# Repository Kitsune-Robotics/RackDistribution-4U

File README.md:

# RackDistribution-4U

This repo contains all the firmware and hardware for the RackDistribution-4U.
If you're looking for the latest docs/builds, see our [Releases Page](https://github.com/Kitsune-Robotics/RackDistribution-4U/releases).

# Getting Started

First, clone this repo (and optionally checkout a branch)

```shell
git clone https://github.com/Kitsune-Robotics/RackDistribution-4U.git --recursive
cd RackDistribution-4U
```

# Init Submodules

Some libraries and resources are included as submodules, run the following
command to initialize them before opening the main sch

(If you get a missing library error, make sure to do this)

```shell
git submodule update --init --recursive
```

## Project Layout

If you want to use this project template for yourself, you can find it [here!](https://github.com/Kitsune-Robotics/Project-Template)

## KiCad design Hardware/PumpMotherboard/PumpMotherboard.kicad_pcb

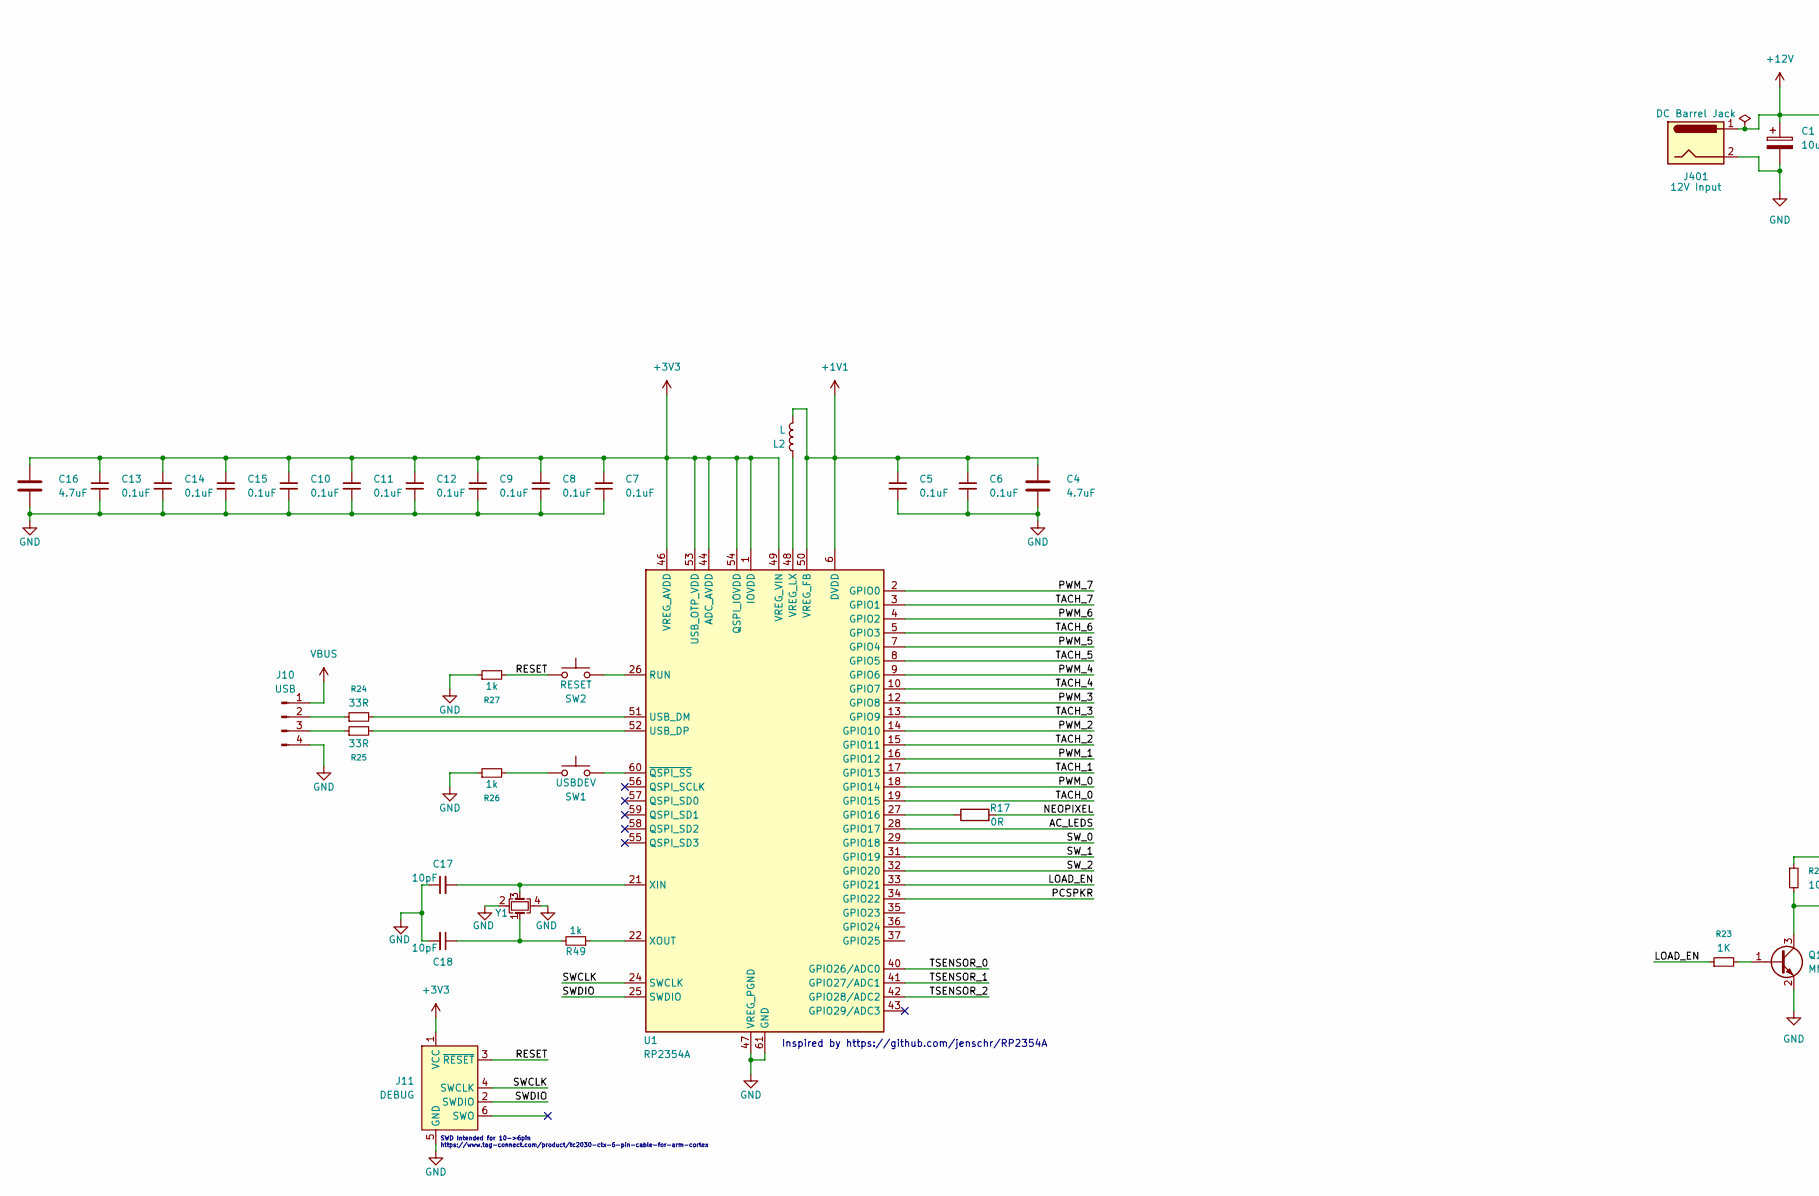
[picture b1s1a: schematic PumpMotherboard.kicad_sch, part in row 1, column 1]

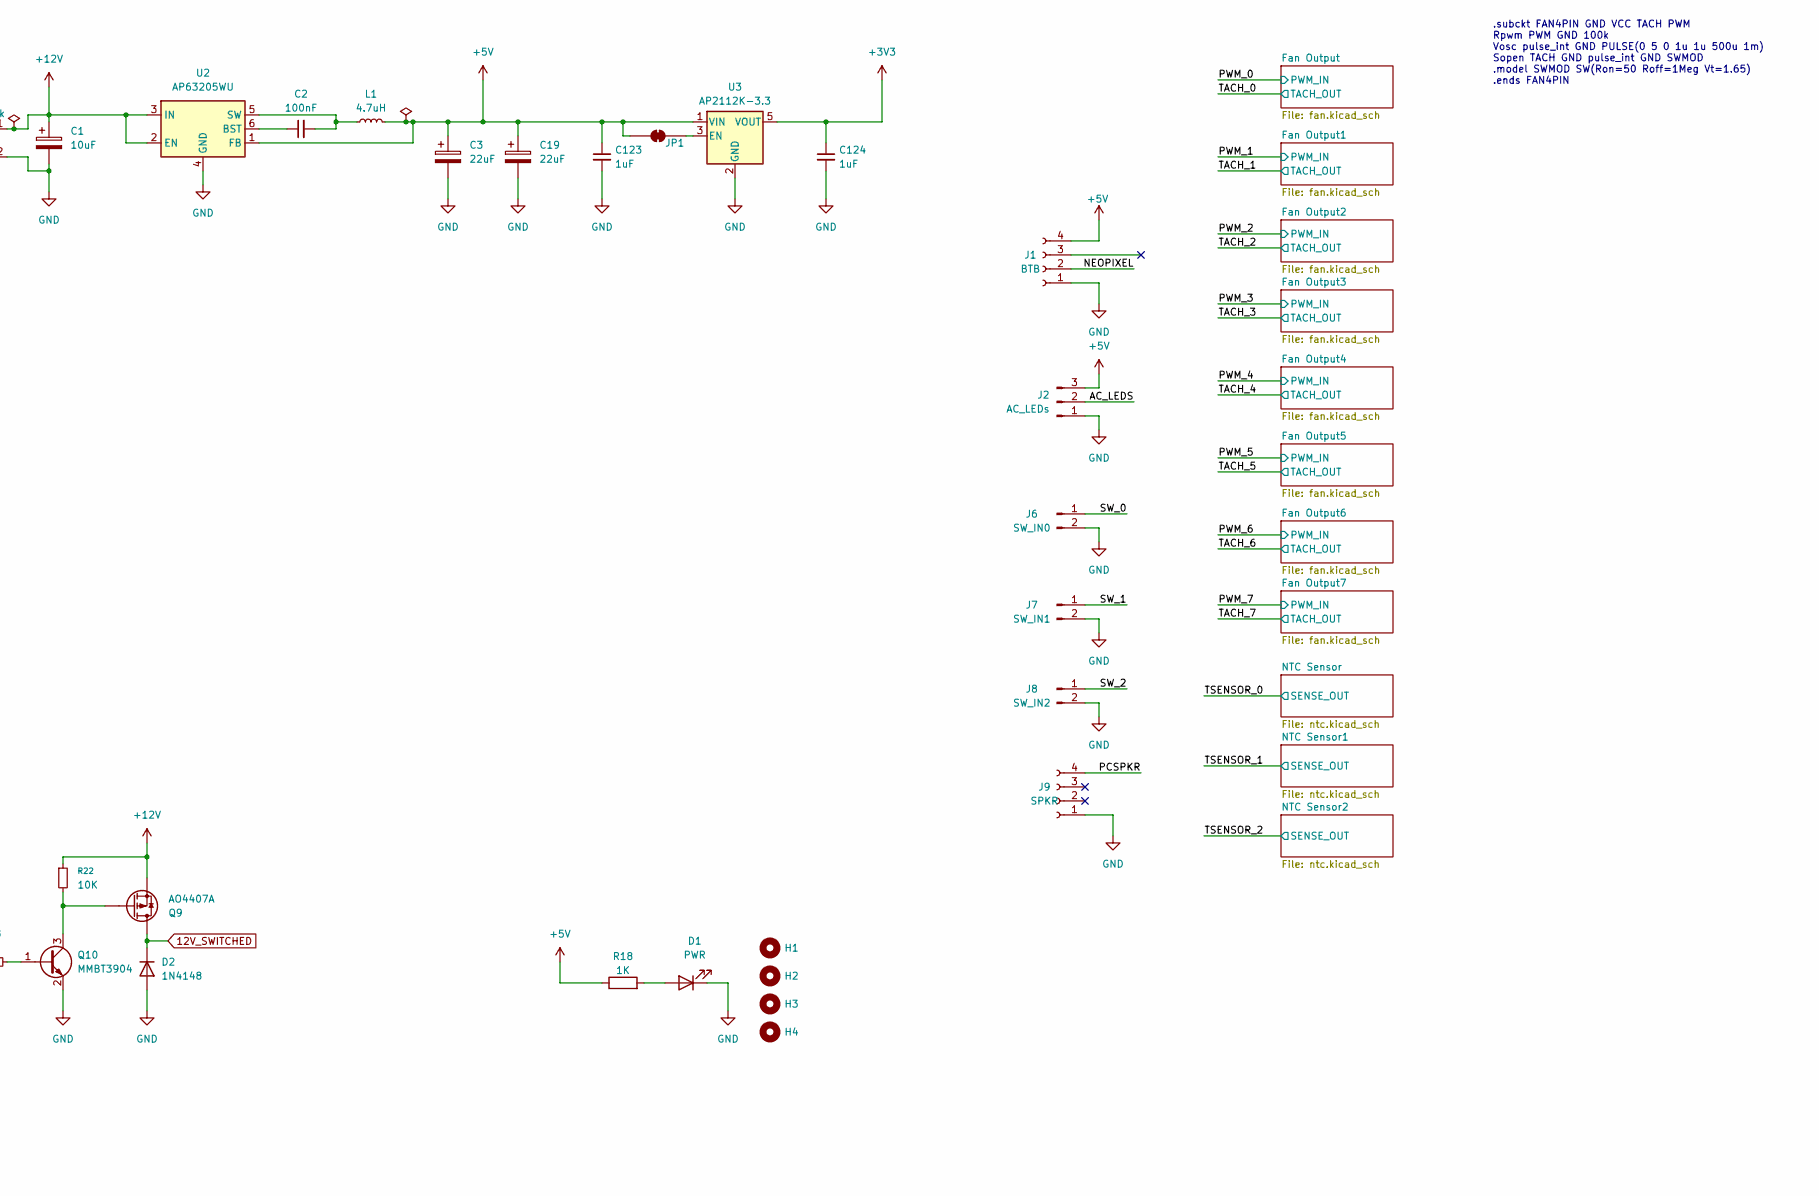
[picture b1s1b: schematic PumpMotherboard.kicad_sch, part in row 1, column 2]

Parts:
C1: 10uF; CP_Elec_4x3
C2: 100nF; C_0805_2012Metric
C3, C19: 22uF; CP_Elec_6.3x7.7; LCSC# C46550391
C4, C16: 4.7uF; C_0805_2012Metric
C5, C6, C7, C8, C9, C10, C11, C12, C13, C14, C15: 0.1uF; C_0402_1005Metric
C17, C18: 10pF; C_0603_1608Metric; MPN CL10C100JB8NFNC
C123, C124: 1uF; C_0603_1608Metric; LCSC# C15849
D1: PWR; LED_0805_2012Metric
D2: 1N4148; D_DO-35_SOD27_P7.62mm_Horizontal
H1, H2, H3, H4: MountingHole; MountingHole_4.3mm_M4
J1: BTB; PinSocket_1x04_P2.54mm_Vertical
J2: AC_LEDs; JST_XH_B3B-XH-A_1x03_P2.50mm_Vertical
J6: SW_IN0; JST_XH_B2B-XH-A_1x02_P2.50mm_Vertical
J7: SW_IN1; JST_XH_B2B-XH-A_1x02_P2.50mm_Vertical
J8: SW_IN2; JST_XH_B2B-XH-A_1x02_P2.50mm_Vertical
J9: SPKR; PinHeader_1x04_P2.54mm_Vertical
J10: USB; JST_XH_B4B-XH-A_1x04_P2.50mm_Vertical
J11: DEBUG; Tag-Connect_TC2030-IDC-FP_2x03_P1.27mm_Vertical
J401: 12V Input; BarrelJack_GCT_DCJ200-10-A_Horizontal
JP1: SolderJumper_2_Bridged; SolderJumper-2_P1.3mm_Bridged2Bar_RoundedPad1.0x1.5mm
L1: 4.7uH; L_APV_ANR4012; LCSC# C467061
L2: L; L_0805_2012Metric
Q9: AO4407A; SOIC-8_5.3x5.3mm_P1.27mm
Q10: MMBT3904; SOT-23
R17: 0R; R_0805_2012Metric
R18, R23: 1K; R_0805_2012Metric
R22: 10K; R_0805_2012Metric
R24, R25: 33R; R_0805_2012Metric
R26, R27: 1k; R_0805_2012Metric
R49: 1k; R_0603_1608Metric
SW1: USBDEV; SW_PUSH_6mm
SW2: RESET; SW_PUSH_6mm
U1: RP2354A; QFN-60-1EP_7x7mm_P0.4mm_EP3.4x3.4mm
U2: AP63205WU; TSOT-23-6; LCSC# C2071056
U3: AP2112K-3.3; SOT-23-5; LCSC# C51118
Y1: Crystal; Crystal_SMD_3225-4Pin_3.2x2.5mm; MPN ABM8-272-T3

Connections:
12V_SWITCHED: D2.1 (K), Q9.5 (D), Q9.6 (D), Q9.7 (D), Q9.8 (D); also elsewhere on the board
+1V1: C4.1, C5.1, C6.1, L2.2, U1.6 (DVDD), U1.23 (DVDD), U1.39 (DVDD), U1.50 (VREG_FB)
+3V3: C7.1, C8.1, C9.1, C10.1, C11.1, C12.1, C13.1, C14.1, C15.1, C16.1, C124.1, J11.1 (VCC), U1.1 (IOVDD), U1.11 (IOVDD), U1.20 (IOVDD), U1.30 (IOVDD), U1.38 (IOVDD), U1.44 (ADC_AVDD), U1.45 (IOVDD), U1.46 (VREG_AVDD), U1.49 (VREG_VIN), U1.53 (USB_OTP_VDD), U1.54 (QSPI_IOVDD), U3.5 (VOUT); also elsewhere on the board
+5V: C3.1, C19.1, C123.1, J1.4, J2.3, JP1.1 (A), L1.2, R18.1, U2.1 (FB), U3.1 (VIN)
+12V: C1.1, J401.1, Q9.1 (S), Q9.2 (S), Q9.3 (S), R22.1, U2.2 (EN), U2.3 (IN)
/AC_LEDS: J2.2, U1.28 (GPIO17)
/LOAD_EN: R23.1, U1.33 (GPIO21)
/NEOPIXEL: J1.2, R17.2; also elsewhere on the board
/PCSPKR: J9.4, U1.34 (GPIO22)
/PWM_0: U1.18 (GPIO14); also elsewhere on the board
/PWM_1: U1.16 (GPIO12); also elsewhere on the board
/PWM_2: U1.14 (GPIO10); also elsewhere on the board
/PWM_3: U1.12 (GPIO8); also elsewhere on the board
/PWM_4: U1.9 (GPIO6); also elsewhere on the board
/PWM_5: U1.7 (GPIO4); also elsewhere on the board
/PWM_6: U1.4 (GPIO2); also elsewhere on the board
/PWM_7: U1.2 (GPIO0); also elsewhere on the board
/RESET: J11.3 (~RESET), R27.2, SW2.1
/SWCLK: J11.4 (SWCLK), U1.24 (SWCLK)
/SWDIO: J11.2 (SWDIO), U1.25 (SWDIO)
/SW_0: J6.1, U1.29 (GPIO18)
/SW_1: J7.1, U1.31 (GPIO19)
/SW_2: J8.1, U1.32 (GPIO20)
/TACH_1: U1.17 (GPIO13); also elsewhere on the board
/TACH_2: U1.15 (GPIO11); also elsewhere on the board
/TACH_3: U1.13 (GPIO9); also elsewhere on the board
/TACH_4: U1.10 (GPIO7); also elsewhere on the board
/TACH_5: U1.8 (GPIO5); also elsewhere on the board
/TACH_6: U1.5 (GPIO3); also elsewhere on the board
/TACH_7: U1.3 (GPIO1); also elsewhere on the board
/TSENSOR_0: U1.40 (GPIO26/ADC0); also elsewhere on the board
/TSENSOR_1: U1.41 (GPIO27/ADC1); also elsewhere on the board
/TSENSOR_2: U1.42 (GPIO28/ADC2); also elsewhere on the board
GND: C1.2, C3.2, C4.2, C5.2, C6.2, C7.2, C8.2, C9.2, C10.2, C11.2, C12.2, C13.2, C14.2, C15.2, C16.2, C17.1, C18.2, C19.2, C123.2, C124.2, D1.1 (K), D2.2 (A), J1.1, J2.1, J6.2, J7.2, J8.2, J9.1, J10.4, J11.5 (GND), J401.2, Q10.2 (E), R26.1, R27.1, U1.47 (VREG_PGND), U1.61 (GND), U2.4 (GND), U3.2 (GND), Y1.2, Y1.4; also elsewhere on the board
unnamed: C18.1, R49.2, Y1.1
unnamed: D1.2 (A), R18.2
unnamed: J10.3, R25.1
unnamed: JP1.2 (B), U3.3 (EN)
unnamed: Q10.1 (B), R23.2
unnamed: Q9.4 (G), Q10.3 (C), R22.2
unnamed: R26.2, SW1.1
unnamed: R17.1, U1.27 (GPIO16)
unnamed: SW2.2, U1.26 (RUN)
unnamed: R25.2, U1.52 (USB_DP)
unnamed: L2.1, U1.48 (VREG_LX)
unnamed: C17.2, U1.21 (XIN), Y1.3
unnamed: R49.1, U1.22 (XOUT)
unnamed: SW1.2, U1.60 (~QSPI_SS)
unnamed: C2.1, U2.6 (BST)
unnamed: C2.2, L1.1, U2.5 (SW)
VBUS: J10.1

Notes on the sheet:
SWD Intended for 10->6pin https://www.tag-connect.com/product/tc2030-ctx-6-pin-cable-for-arm-cortex
Inspired by https://github.com/jenschr/RP2354A
.subckt FAN4PIN GND VCC TACH PWM Rpwm PWM GND 100k Vosc pulse_int GND PULSE(0 5 0 1u 1u 500u 1m) Sopen TACH GND pulse_int GND SWMOD .model SWMOD SW(Ron=50 Roff=1Meg Vt=1.65) .ends FAN4PIN

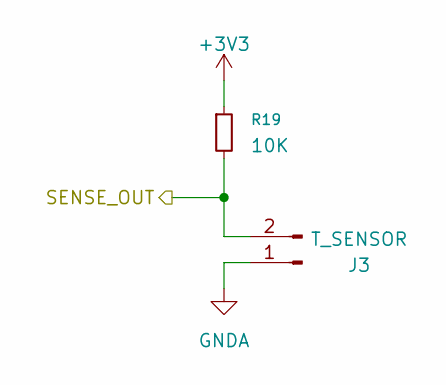
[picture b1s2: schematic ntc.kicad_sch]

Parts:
J3: T_SENSOR; PinHeader_1x02_P2.54mm_Vertical
R19: 10K; R_0805_2012Metric

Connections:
+3V3: R19.1; also elsewhere on the board
/TSENSOR_0: J3.2, R19.2; also elsewhere on the board
GNDA: J3.1; also elsewhere on the board

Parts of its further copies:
J4, J5: T_SENSOR; PinHeader_1x02_P2.54mm_Vertical
R20, R21: 10K; R_0805_2012Metric

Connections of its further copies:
+3V3: R20.1, R21.1; also elsewhere on the board
/TSENSOR_1: J4.2, R20.2; also elsewhere on the board
/TSENSOR_2: J5.2, R21.2; also elsewhere on the board
GNDA: J4.1, J5.1; also elsewhere on the board

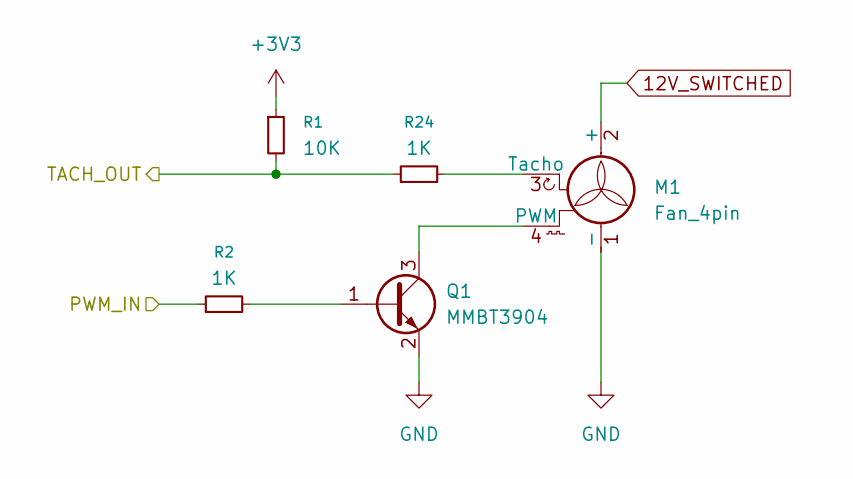
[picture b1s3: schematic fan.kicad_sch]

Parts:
M1: Fan_4pin; FanPinHeader_1x04_P2.54mm_Vertical; LCSC# C240840
Q1: MMBT3904; SOT-23
R1: 10K; R_0805_2012Metric
R2, R24: 1K; R_0805_2012Metric

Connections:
12V_SWITCHED: M1.2 (+); also elsewhere on the board
+3V3: R1.1; also elsewhere on the board
/PWM_0: R2.1; also elsewhere on the board
GND: M1.1 (-), Q1.2 (E); also elsewhere on the board
unnamed: M1.4 (PWM), Q1.3 (C)
unnamed: Q1.1 (B), R2.2

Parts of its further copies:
M2, M3, M4, M5, M6, M7, M8: Fan_4pin; FanPinHeader_1x04_P2.54mm_Vertical; LCSC# C240840
Q2, Q3, Q4, Q5, Q6, Q7, Q8: MMBT3904; SOT-23
R3, R5, R7, R9, R11, R13, R15: 1K; R_0805_2012Metric
R4, R6, R8, R10, R12, R14, R16: 10K; R_0805_2012Metric

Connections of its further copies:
12V_SWITCHED: M2.2 (+), M3.2 (+), M4.2 (+), M5.2 (+), M6.2 (+), M7.2 (+), M8.2 (+); also elsewhere on the board
+3V3: R4.1, R6.1, R8.1, R10.1, R12.1, R14.1, R16.1; also elsewhere on the board
/PWM_1: R3.1; also elsewhere on the board
/PWM_2: R5.1; also elsewhere on the board
/PWM_3: R7.1; also elsewhere on the board
/PWM_4: R9.1; also elsewhere on the board
/PWM_5: R11.1; also elsewhere on the board
/PWM_6: R13.1; also elsewhere on the board
/PWM_7: R15.1; also elsewhere on the board
/TACH_1: M2.3 (Tacho), R4.2; also elsewhere on the board
/TACH_2: M3.3 (Tacho), R6.2; also elsewhere on the board
/TACH_3: M4.3 (Tacho), R8.2; also elsewhere on the board
/TACH_4: M5.3 (Tacho), R10.2; also elsewhere on the board
/TACH_5: M6.3 (Tacho), R12.2; also elsewhere on the board
/TACH_6: M7.3 (Tacho), R14.2; also elsewhere on the board
/TACH_7: M8.3 (Tacho), R16.2; also elsewhere on the board
GND: M2.1 (-), M3.1 (-), M4.1 (-), M5.1 (-), M6.1 (-), M7.1 (-), M8.1 (-), Q2.2 (E), Q3.2 (E), Q4.2 (E), Q5.2 (E), Q6.2 (E), Q7.2 (E), Q8.2 (E); also elsewhere on the board
unnamed: M2.4 (PWM), Q2.3 (C)
unnamed: M3.4 (PWM), Q3.3 (C)
unnamed: M4.4 (PWM), Q4.3 (C)
unnamed: M5.4 (PWM), Q5.3 (C)
unnamed: M6.4 (PWM), Q6.3 (C)
unnamed: M7.4 (PWM), Q7.3 (C)
unnamed: M8.4 (PWM), Q8.3 (C)
unnamed: Q2.1 (B), R3.2
unnamed: Q3.1 (B), R5.2
unnamed: Q4.1 (B), R7.2
unnamed: Q5.1 (B), R9.2
unnamed: Q6.1 (B), R11.2
unnamed: Q7.1 (B), R13.2
unnamed: Q8.1 (B), R15.2

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
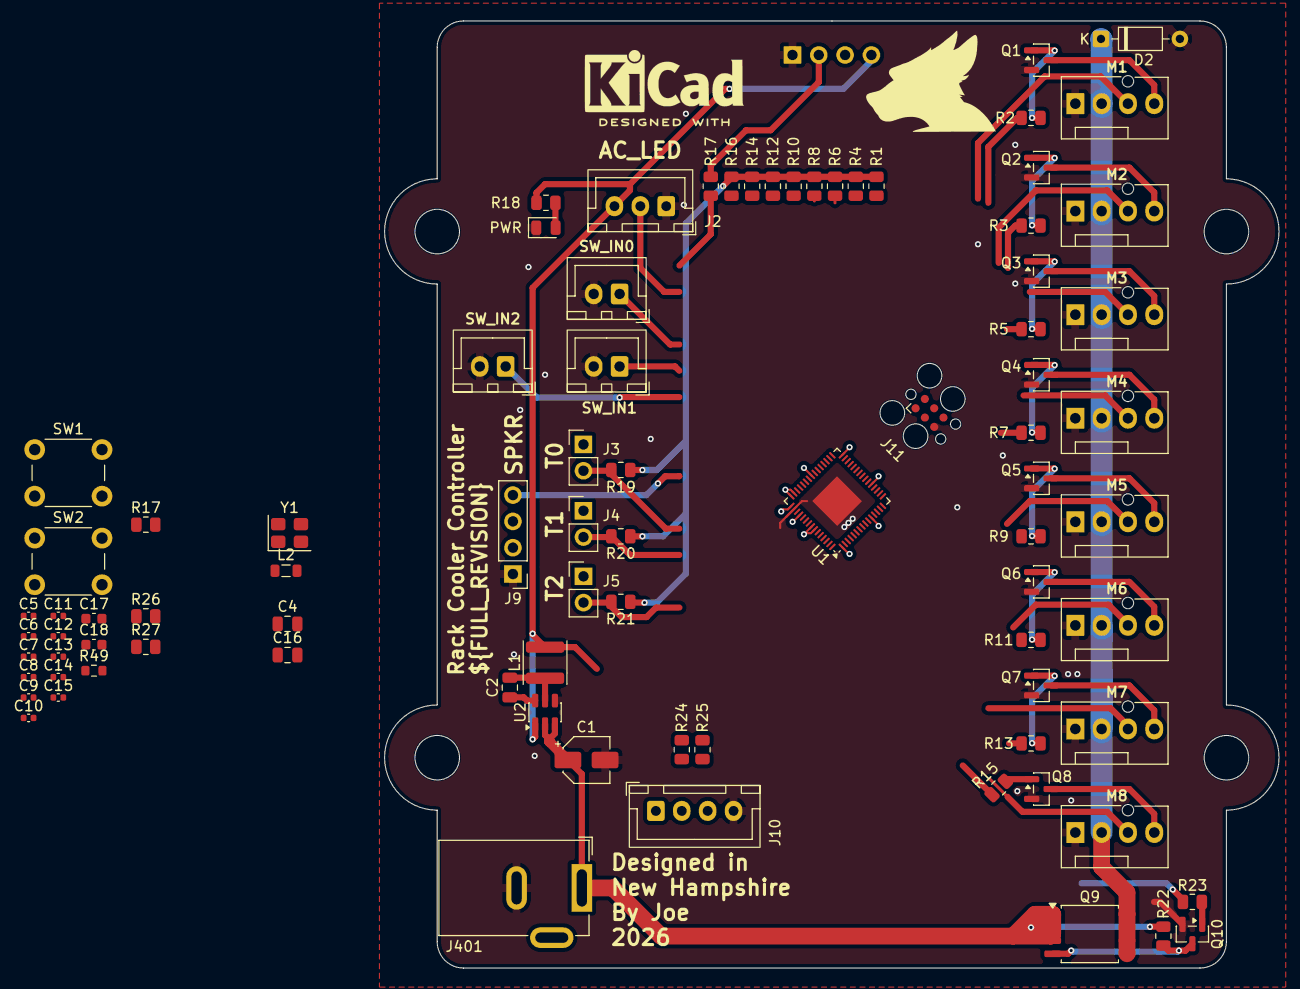
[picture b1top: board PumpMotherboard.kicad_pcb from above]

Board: 2 copper layers, 86.4 x 91.4 mm, 89 parts (1 on the bottom side), 69 nets.

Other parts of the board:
R17#2: 0R; R_0805_2012Metric

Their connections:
/NEOPIXEL: R17#2.2; also elsewhere on the board

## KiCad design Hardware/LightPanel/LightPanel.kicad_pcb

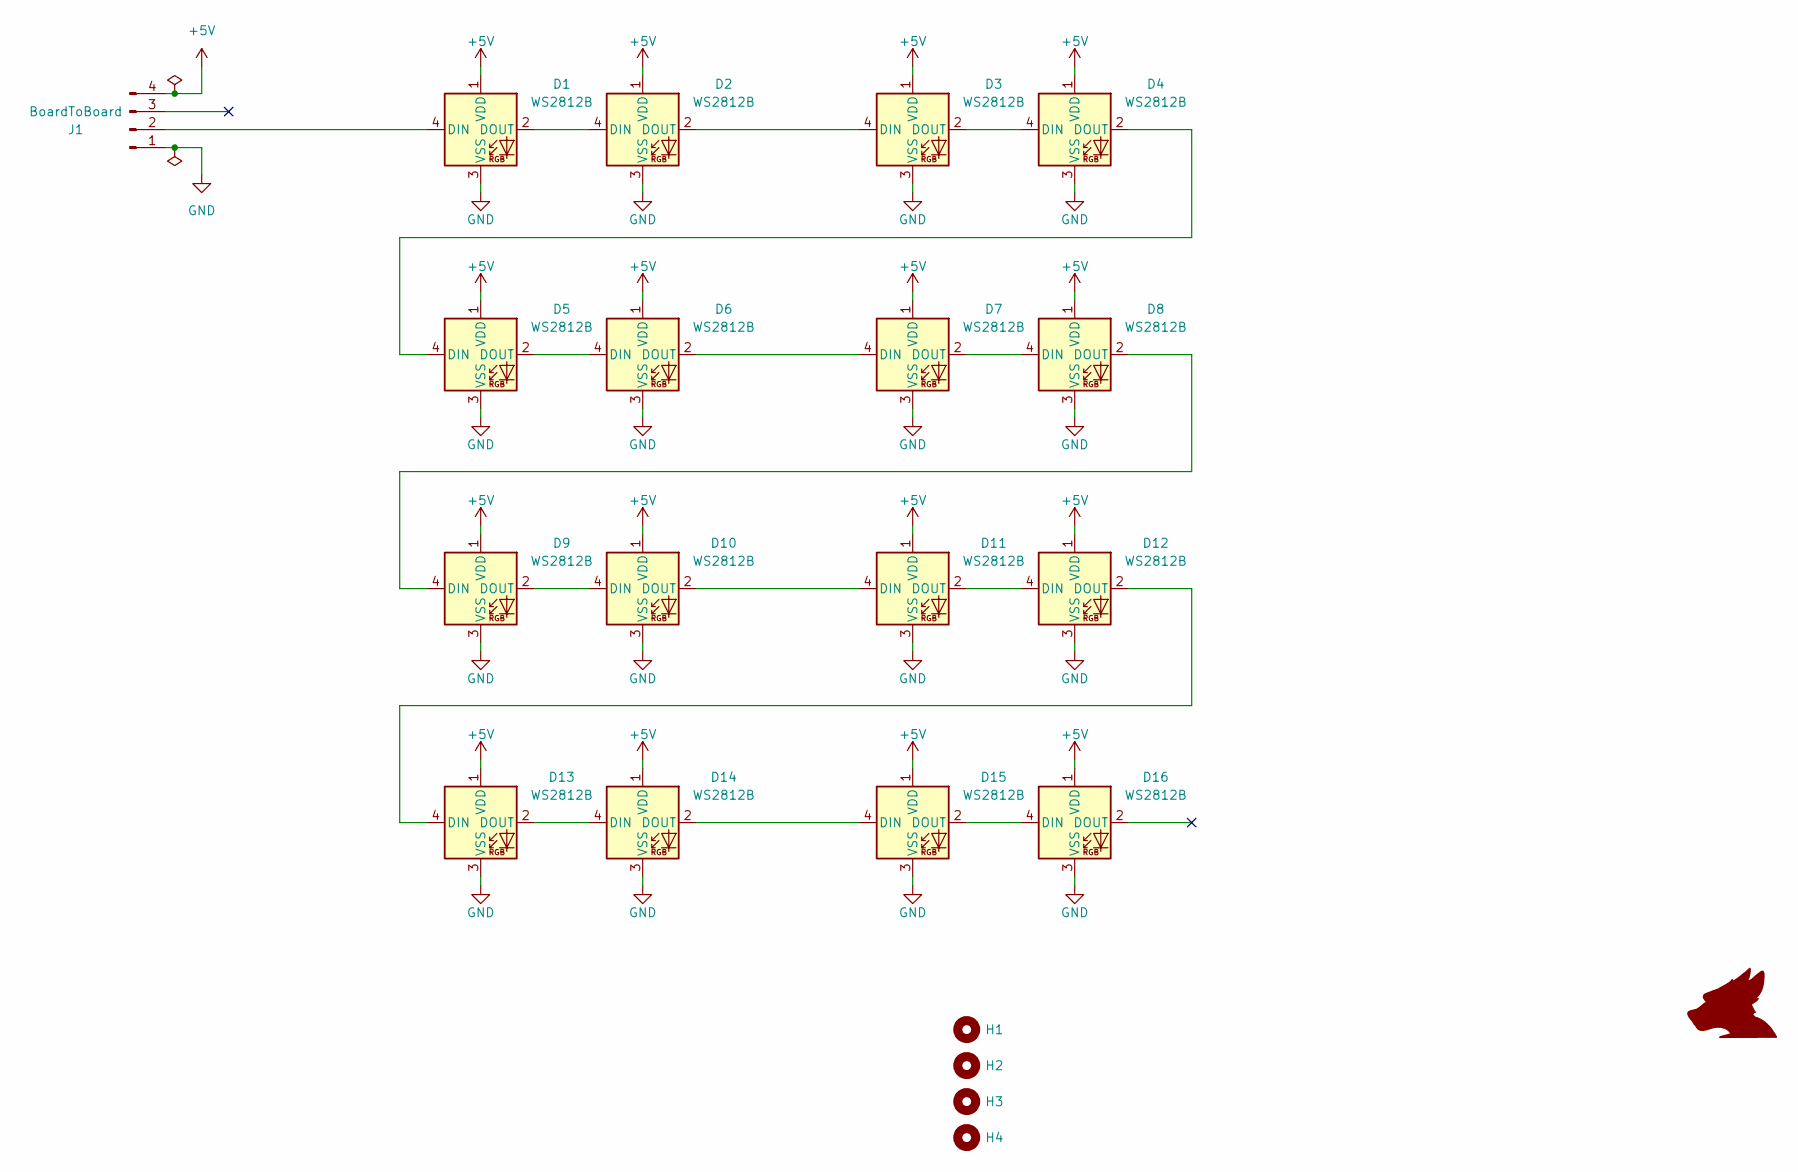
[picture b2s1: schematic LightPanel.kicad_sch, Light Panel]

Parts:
D1, D2, D3, D4, D5, D6, D7, D8, D9, D10, D11, D12, D13, D14, D15, D16: WS2812B; LED_WS2812B_PLCC4_5.0x5.0mm_P3.2mm; LCSC# C52917433
H1, H2, H3, H4: MountingHole; MountingHole_4.3mm_M4
J1: BoardToBoard; PinHeader_1x04_P2.54mm_Vertical

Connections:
+5V: D1.1 (VDD), D2.1 (VDD), D3.1 (VDD), D4.1 (VDD), D5.1 (VDD), D6.1 (VDD), D7.1 (VDD), D8.1 (VDD), D9.1 (VDD), D10.1 (VDD), D11.1 (VDD), D12.1 (VDD), D13.1 (VDD), D14.1 (VDD), D15.1 (VDD), D16.1 (VDD), J1.4
GND: D1.3 (VSS), D2.3 (VSS), D3.3 (VSS), D4.3 (VSS), D5.3 (VSS), D6.3 (VSS), D7.3 (VSS), D8.3 (VSS), D9.3 (VSS), D10.3 (VSS), D11.3 (VSS), D12.3 (VSS), D13.3 (VSS), D14.3 (VSS), D15.3 (VSS), D16.3 (VSS), J1.1
unnamed: D1.4 (DIN), J1.2
unnamed: D1.2 (DOUT), D2.4 (DIN)
unnamed: D2.2 (DOUT), D3.4 (DIN)
unnamed: D3.2 (DOUT), D4.4 (DIN)
unnamed: D4.2 (DOUT), D5.4 (DIN)
unnamed: D5.2 (DOUT), D6.4 (DIN)
unnamed: D6.2 (DOUT), D7.4 (DIN)
unnamed: D7.2 (DOUT), D8.4 (DIN)
unnamed: D8.2 (DOUT), D9.4 (DIN)
unnamed: D9.2 (DOUT), D10.4 (DIN)
unnamed: D10.2 (DOUT), D11.4 (DIN)
unnamed: D11.2 (DOUT), D12.4 (DIN)
unnamed: D12.2 (DOUT), D13.4 (DIN)
unnamed: D13.2 (DOUT), D14.4 (DIN)
unnamed: D14.2 (DOUT), D15.4 (DIN)
unnamed: D15.2 (DOUT), D16.4 (DIN)

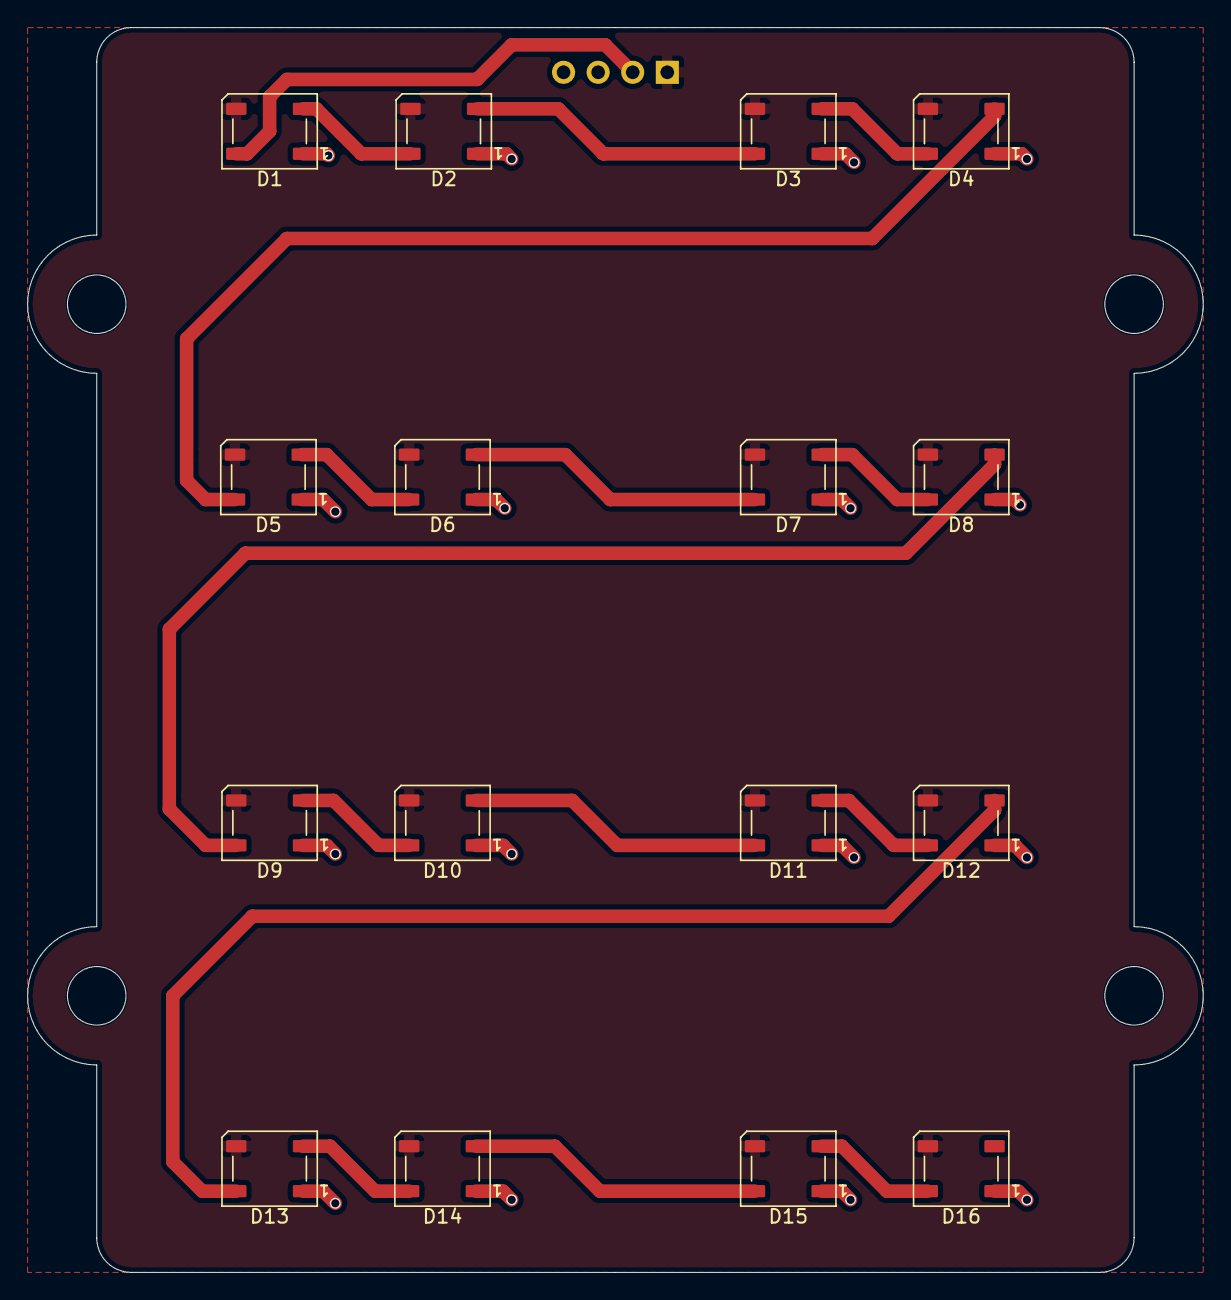
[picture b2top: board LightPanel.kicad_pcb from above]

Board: 2 copper layers, 86.4 x 91.4 mm, 21 parts (1 on the bottom side), 18 nets.

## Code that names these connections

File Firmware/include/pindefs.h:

#pragma once

// Fan PWM / tach (GPIO)
#define PWM_7_PIN 0
#define TACH_7_PIN 1
#define PWM_6_PIN 2
#define TACH_6_PIN 3
#define PWM_5_PIN 4
#define TACH_5_PIN 5
#define PWM_4_PIN 6
#define TACH_4_PIN 7
#define PWM_3_PIN 8
#define TACH_3_PIN 9
#define PWM_2_PIN 10
#define TACH_2_PIN 11
#define PWM_1_PIN 12
#define TACH_1_PIN 13
#define PWM_0_PIN 14
#define TACH_0_PIN 15

// Panel
#define NEOPIXEL_PIN 16
#define NEOPIXEL_NUM_PIXELS 16
#define NEOPIXEL_FREQ_HZ 800000.0f
#define AC_LEDS_PIN 17
#define AC_LEDS_NUM_PIXELS 50 // idk the exact length

// Switches
#define SW_0_PIN 18 // inhibit
#define SW_1_PIN 19 // max cooling
#define SW_2_PIN 20 // mute
#define SW_INHIBIT_PIN SW_0_PIN
#define SW_MAX_COOL_PIN SW_1_PIN
#define SW_MUTE_PIN SW_2_PIN

#define LOAD_EN_PIN 21
#define PCSPKR_PIN 22
#define USB_VBUS_PIN 24 /* Pico module VBUS divider*/

// Temperature (GPIO / ADC channel)
#define TSENSOR_0_PIN 26 /* coolant */
#define TSENSOR_0_ADC_CH 0
#define TSENSOR_1_PIN 27 /* air */
#define TSENSOR_1_ADC_CH 1
#define TSENSOR_2_PIN 28 /* exhaust (optional) */
#define TSENSOR_2_ADC_CH 2

#define TSENSOR_PULLUP_OHMS 10000.0f
#define NTC_R25_OHMS 10000.0f
#define NTC_BETA 3950.0f
#define NTC_SHORT_RAW 32
#define NTC_OPEN_RAW 3900 /* ~200k / -30 C; unplugged sits near the 3V3 rail */
